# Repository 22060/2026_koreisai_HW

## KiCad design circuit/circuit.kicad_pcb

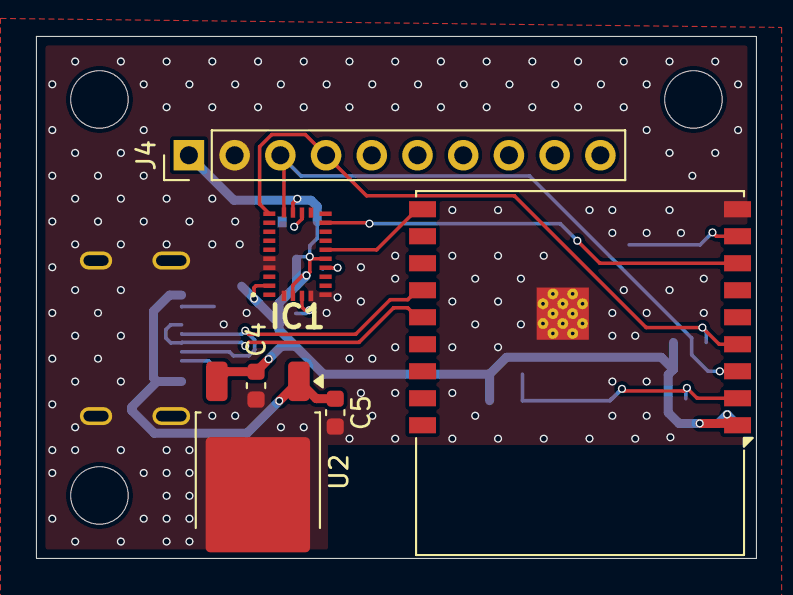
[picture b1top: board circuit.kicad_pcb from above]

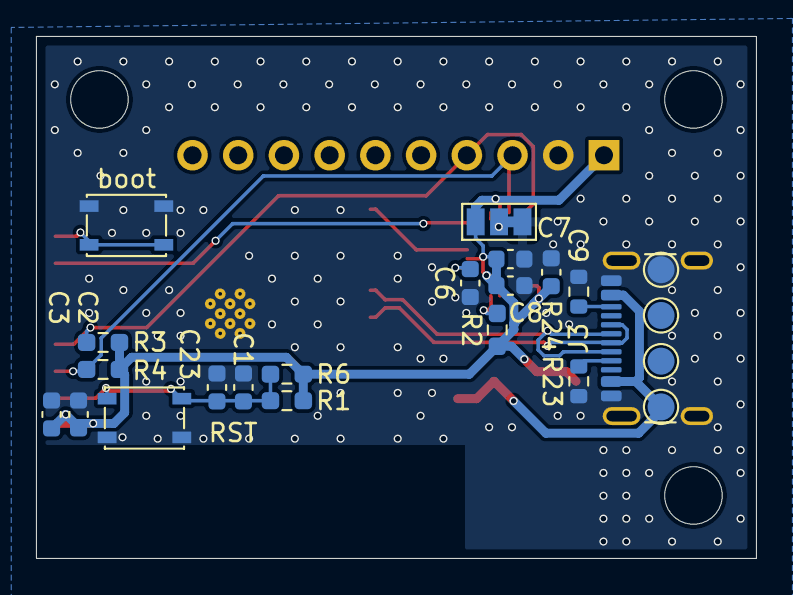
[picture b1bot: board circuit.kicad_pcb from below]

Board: 2 copper layers, 40.0 x 29.0 mm, 32 parts (23 on the bottom side), 16 nets.

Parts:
C1, C8: 1u; C_0603_1608Metric
C2, C4, C5: 10u; C_0603_1608Metric
C3, C6, C7, C9, C23: 0.1u; C_0603_1608Metric
H1, H2, H3: MountingHole; MountingHole_3.2mm_M3
IC1: BNO085
J3: USB_C_Receptacle_USB2.0; USB_C_Receptacle_GCT_USB4105-xx-A_16P_TopMnt_Horizontal
J4: Conn_01x10_Pin; PinHeader_1x10_P2.54mm_Vertical
JP1: Jumper_3_Bridged12; SolderJumper-3_P1.3mm_Bridged12_Pad1.0x1.5mm_NumberLabels
R1, R2, R6: 10k; R_0603_1608Metric_Pad0.98x0.95mm_HandSolder
R3, R4: 4.7k; R_0603_1608Metric_Pad0.98x0.95mm_HandSolder
R23, R24: 5.1k; R_0603_1608Metric
RST: SW_Push; SW_SPST_PTS810
TP1, TP2, TP3, TP4: TestPoint; TestPoint_Pad_D1.5mm
U1: ESP32-C3-WROOM-02
U2: BD33FC0FP; TO-252-2
boot: SW_Push; SW_SPST_PTS810

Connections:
+3.3V: C2.2, C3.2, C4.1, C7.1, C8.1, C9.1, IC1.3 (VDD), IC1.10 (CLKSEL0), IC1.18 (H_CSN), IC1.28 (VDDIO), J4.1, JP1.3 (B), R1.2, R2.1, R3.1, R4.1, R6.2, U1.1 (3V3), U2.3 (VO)
+5V: C5.1, J3.A4 (VBUS), J3.A9 (VBUS), J3.B4 (VBUS), J3.B9 (VBUS), TP1.1, U2.1 (VCC)
BOOT: U1.8 (IO9), boot.2
D+: J3.A6 (D+), J3.B6 (D+), U1.14 (IO19)
D-: J3.A7 (D-), J3.B7 (D-), U1.13 (IO18)
GND: C1.2, C2.1, C3.1, C4.2, C5.2, C6.1, C7.2, C8.2, C9.2, C23.2, IC1.2 (GND_1), IC1.5 (PS1), IC1.6 (PS0/WAKE), IC1.25 (GND_2), IC1.26 (XOUT32/CLKSEL1), J3.A1 (GND), J3.A12 (GND), J3.B1 (GND), J3.B12 (GND), J3.S1 (SHIELD), J4.2, JP1.1 (A), R23.2, R24.2, RST.1, TP4.1, U1.9 (GND), U1.19 (GND), U2.2 (GND), boot.1
NRST: C1.1, C23.1, R1.1, R6.1, RST.2, U1.2 (EN)
unnamed: IC1.4 (BOOTN), R2.2
unnamed: C6.2, IC1.9 (CAP)
unnamed: IC1.17 (SA0/H_MOSI_), JP1.2 (C)
unnamed: J3.A5 (CC1), R23.1
unnamed: J3.B5 (CC2), R24.1
RST_IMU: IC1.11 (NRST), U1.10 (IO10)
SCL: IC1.19 (H_SCL/SCK/RX), J4.3, R4.2, U1.3 (IO4)
SDA: IC1.20 (H_SDA/H_MISO/TX_), J4.4, R3.2, U1.4 (IO5)
interupt_imu: IC1.14 (H_INTN), U1.7 (IO8)

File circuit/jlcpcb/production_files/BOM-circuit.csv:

Comment,Designator,Footprint,LCSC,Quantity
0.1u,C23,C_0603_1608Metric,C52923,1
10k,R6,R_0603_1608Metric_Pad0.98x0.95mm_HandSolder,C25744,1
5.1k,"R23,R24",R_0603_1608Metric,C23186,2
10k,R1,R_0603_1608Metric_Pad0.98x0.95mm_HandSolder,,1
1u,C1,C_0603_1608Metric,,1
1u,C8,C_0603_1608Metric,,1
0.1u,C7,C_0603_1608Metric,,1
0.1u,C6,C_0603_1608Metric,,1
10k,R2,R_0603_1608Metric_Pad0.98x0.95mm_HandSolder,,1
BNO085,IC1,BNO085,,1
0.1u,C9,C_0603_1608Metric,,1
TestPoint,TP2,TestPoint_Pad_D1.5mm,,1
10u,C4,C_0603_1608Metric,,1
10u,C5,C_0603_1608Metric,,1
TestPoint,TP4,TestPoint_Pad_D1.5mm,,1
TestPoint,TP3,TestPoint_Pad_D1.5mm,,1
BD33FC0FP,U2,TO-252-2,,1
USB_C_Receptacle_USB2.0,J3,USB_C_Receptacle_GCT_USB4105-xx-A_16P_TopMnt_Horizontal,,1
TestPoint,TP1,TestPoint_Pad_D1.5mm,,1
ESP32-C3-WROOM-02,U1,ESP32-C3-WROOM-02,,1
Conn_01x10_Pin,J4,PinHeader_1x10_P2.54mm_Vertical,,1
10u,C2,C_0603_1608Metric,,1
4.7k,R3,R_0603_1608Metric_Pad0.98x0.95mm_HandSolder,,1
4.7k,R4,R_0603_1608Metric_Pad0.98x0.95mm_HandSolder,,1
0.1u,C3,C_0603_1608Metric,,1
SW_Push,RST,SW_SPST_PTS810,,1
SW_Push,boot,SW_SPST_PTS810,,1
